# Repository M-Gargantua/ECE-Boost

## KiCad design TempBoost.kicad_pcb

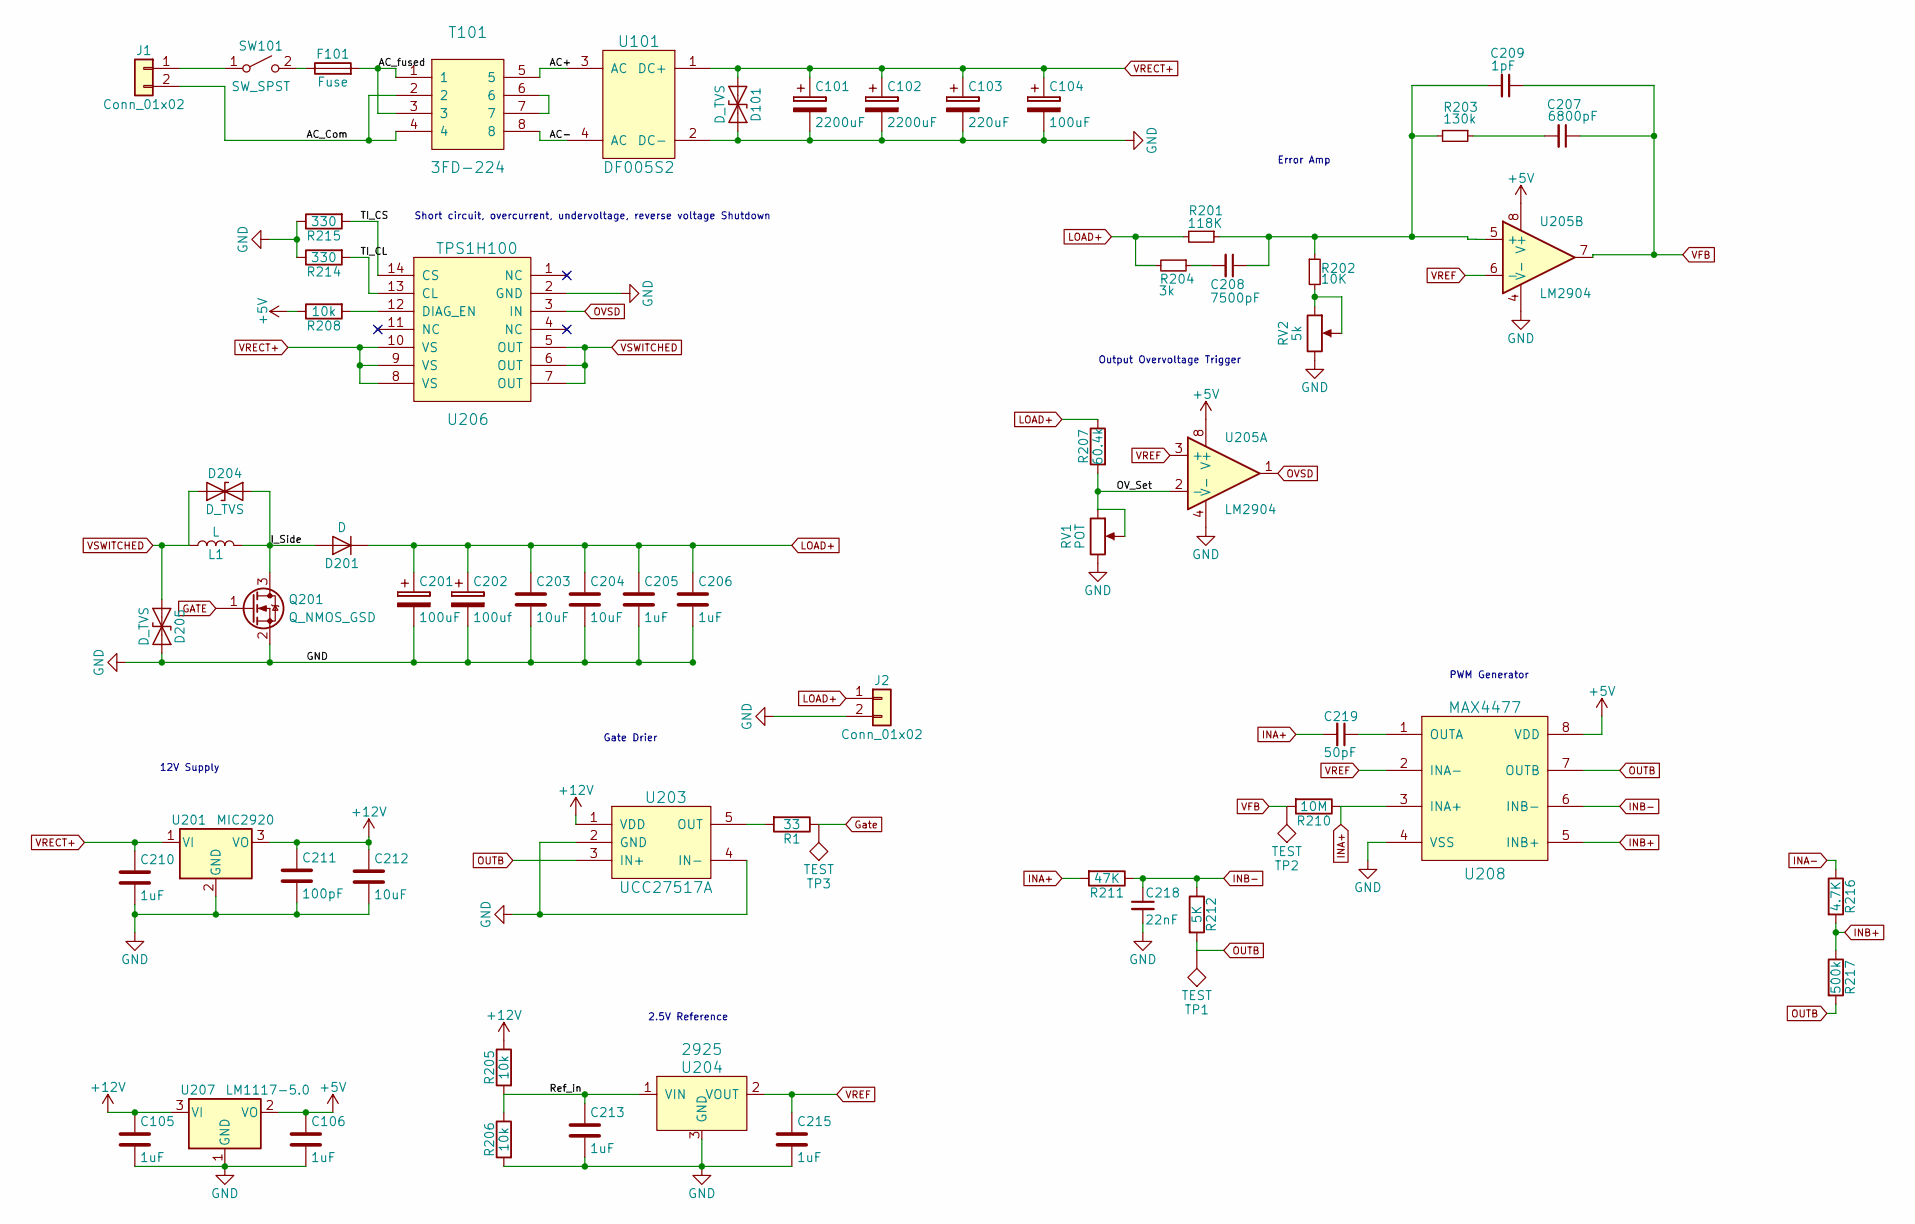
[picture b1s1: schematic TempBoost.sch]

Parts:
C101, C102: 2200uF; CP_Elec_19x19
C103: 220uF; CP_Radial_D12.5mm_P5.00mm
C104, C201: 100uF; CP_Elec_6.3x7.7
C105, C106, C205, C206, C210, C213, C215: 1uF; C_0805
C202: 100uf; CP_Elec_6.3x7.7
C203, C204, C212: 10uF; C_0805
C207: 6800pF; C_0603
C208: 7500pF; C_0603
C209: 1pF; C_0603
C211: 100pF; C_0603_HandSoldering; Part Number C0603C101K3RACTU
C218: 22nF; C_Disc_D5.0mm_W2.5mm_P2.50mm
C219: 50pF; C_0603
D101, D204, D205: D_TVS; SMAJ40ALFCT; Part Number SMAJ40A
D201: D; RFN10BM3SFHTL
F101: Fuse; SMD-1206_Pol
J1, J2: Conn_01x02; ED1202DS
L1: L; 1140-122K
Q201: Q_NMOS_GSD; SOT-23
R1: 33; R_Axial_DIN0614_L14.3mm_D5.7mm_P20.32mm_Horizontal
R201: 118K; R_0805
R202: 10K; R_0805
R203: 130k; R_0603
R204: 3k; R_0603
R205, R206, R208: 10k; R_0805
R207: 60.4k; R_0805
R210: 10M; R_0805
R211: 47K; R_0603
R212: 5K; R_0603
R214, R215: 330; R_0805
R216: 4.7K; R_0603
R217: 500k; R_0603
RV1: POT; Potentiometer_Trimmer_Bourns_3296W
RV2: 5k; Potentiometer_Trimmer_Bourns_3296W
SW101: SW_SPST; 400MSP1R6BLKM6QE
T101: 3FD-224
TP1, TP2, TP3: TEST; 1pin
U101: DF005S2; DF10S2
U201: MIC2920; SOT-223-3_TabPin2; Part Number MIC2920A-12WS-TR
U203: UCC27517A; SOT-23-5
U204: 2925; SOT-23; Part Number REF2925AIDBZR
U205: LM2904; SOIC-8_3.9x4.9mm_Pitch1.27mm; Part Number LM2904AVQDRQ1
U206: TPS1H100; TSSOP-14-1EP_4.4x5mm_Pitch0.65mm
U207: LM1117-5.0; SOT-223-3_TabPin2
U208: MAX4477; SOIC-8_3.9x4.9mm_Pitch1.27mm

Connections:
+5V: C106.1, R208.1, U205.8 (V+), U207.2 (VO), U208.8 (VDD)
+12V: C105.1, C211.1, C212.1, R205.1, U201.3 (VO), U203.1 (VDD), U207.3 (VI)
/AC+: T101.5, U101.3 (AC)
/AC-: T101.8, U101.4 (AC)
/AC_Com: J1.2, T101.2, T101.4
/AC_fused: F101.2, T101.1, T101.3
/I_Side: D201.2 (A), D204.2 (A2), L1.2, Q201.3 (D)
/OV_Set: R207.2, RV1.1, RV1.2, U205.2 (-)
/Ref_in: C213.1, R205.2, R206.1, U204.1 (VIN)
/TI_CL: R214.2, U206.13 (CL)
/TI_CS: R215.2, U206.14 (CS)
GATE: Q201.1 (G), R1.1, TP3.1
GND: C101.2, C102.2, C103.2, C104.2, C105.2, C106.2, C201.2, C202.2, C203.2, C204.2, C205.2, C206.2, C210.2, C211.2, C212.2, C213.2, C215.2, C218.2, D101.2 (A2), D205.2 (A2), J2.2, Q201.2 (S), R206.2, R214.1, R215.1, RV1.3, RV2.3, U101.2 (DC-), U201.2 (GND), U203.2 (GND), U203.4 (IN-), U204.3 (GND), U205.4 (V-), U206.2 (GND), U207.1 (GND), U208.4 (VSS)
INA+: C219.2, R210.1, R211.2, U208.3 (INA+)
INB+: R216.2, R217.1, U208.5 (INB+)
INB-: C218.1, R211.1, R212.1, U208.6 (INB-)
LOAD+: C201.1, C202.1, C203.1, C204.1, C205.1, C206.1, D201.1 (K), J2.1, R201.2, R204.2, R207.1
unnamed: C207.2, R203.1
unnamed: C208.1, C209.2, R201.1, R202.1, R203.2, U205.5 (+)
unnamed: C208.2, R204.1
unnamed: C219.1, U208.1 (OUTA)
unnamed: F101.1, SW101.2 (B)
unnamed: J1.1, SW101.1 (A)
unnamed: R1.2, U203.5 (OUT)
unnamed: R202.2, RV2.1, RV2.2
unnamed: R208.2, U206.12 (DIAG_EN)
unnamed: T101.6, T101.7
OUTB: R212.2, R217.2, TP1.1, U203.3 (IN+), U208.7 (OUTB)
OVSD: U205.1, U206.3 (IN)
VFB: C207.1, C209.1, R210.2, TP2.1, U205.7
VRECT+: C101.1, C102.1, C103.1, C104.1, C210.1, D101.1 (A1), U101.1 (DC+), U201.1 (VI), U206.8 (VS), U206.9 (VS), U206.10 (VS)
VSWITCHED: D204.1 (A1), D205.1 (A1), L1.1, U206.5 (OUT), U206.6 (OUT), U206.7 (OUT)

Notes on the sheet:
Error Amp
12V Supply
2.5V Reference
Gate Drier
Short circuit, overcurrent, undervoltage, reverse voltage Shutdown
Output Overvoltage Trigger
PWM Generator

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
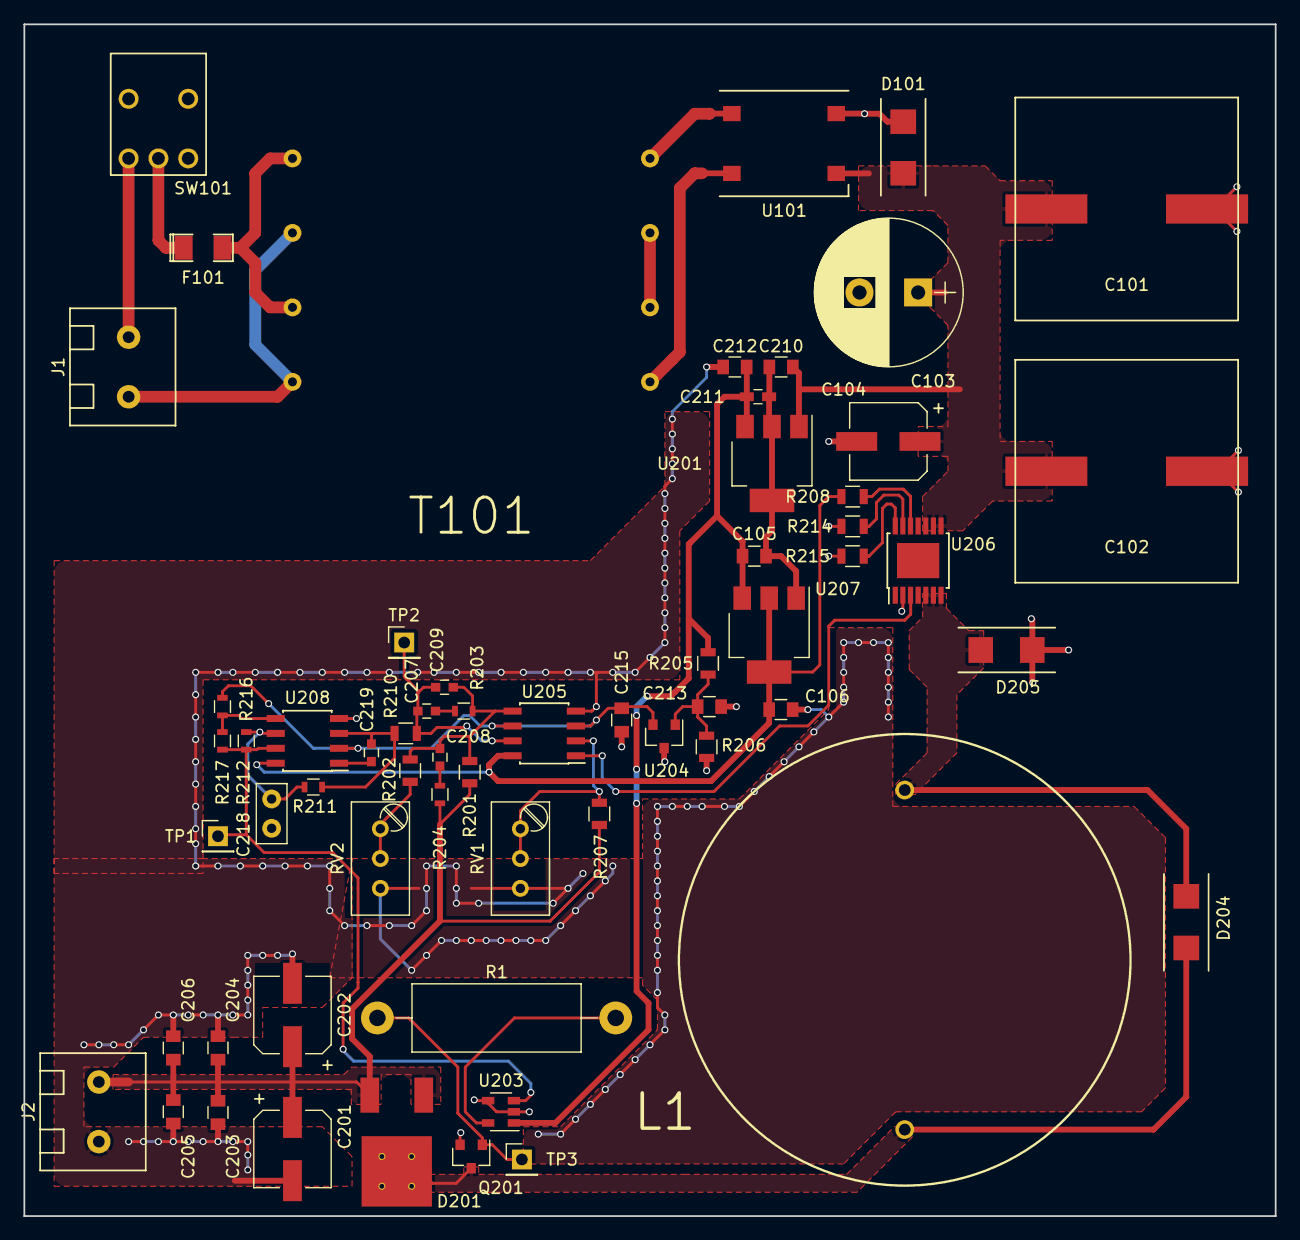
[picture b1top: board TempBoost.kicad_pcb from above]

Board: 2 copper layers, 106.7 x 101.6 mm, 62 parts (0 on the bottom side), 33 nets.

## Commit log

2019-04-03 Initial
2019-04-04 Added OPAx140 Library and added compensator network
2019-04-04 Added Components
2019-04-04 Added Triangle Generator
2019-04-05 Load Switch
2019-04-05 Transformer
2019-04-05 fixed voltage reference
2019-04-05 Changed Triangle Wave
2019-04-05 Need to add back in the PWM
2019-04-05 Added PWM Gen Library
2019-04-08 Create all non standard footprints
2019-04-09 Redid Footprint associations
2019-04-09 Placement again
2019-04-09 Fixed Half of Netlist
2019-04-09 Base Placement
2019-04-09 Starting Layout
2019-04-10 More Routing
    PWM Generator is routed so that it now works but the freqency is 70Hz rather than 70k. RIP
2019-04-11 Done
